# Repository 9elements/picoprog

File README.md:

# Picoprog

Picoprog is a firmware for the Raspberry Pi Pico and STM32 BluePill boards that provides a USB-to-serial and USB-to-SPI bridge. It allows you to communicate with UART and SPI peripherals via USB.

## Prerequisites

Before you can compile and use Picoprog, you need to install the following dependencies:

- Rust and Cargo: Follow the instructions on the [official Rust website](https://www.rust-lang.org/tools/install) to install Rust and Cargo.
- Install flip-link and elf2uf2

```sh
# Only Linux
sudo apt install build-essential libudev-dev pkg-config

# All systems
cargo install flip-link elf2uf2-rs
```

## Compiling the Firmware

To compile the firmware, follow these steps:

1. Clone the repository:

```sh
git clone https://github.com/9elements/picoprog.git
cd picoprog
```

2. Build the firmware for your target device:

For Raspberry Pi Pico:
```sh
cd picoprog
cargo run --release
```

For STM32 BluePill:
```sh
cd bluepill-prog
cargo run --release
```

3. The compiled binary will be located in:
   - Pico: `target/thumbv6m-none-eabi/release` directory
   - BluePill: `target/thumbv7m-none-eabi/release` directory

## Flashing the Firmware

### Raspberry Pi Pico

To flash the firmware onto the Raspberry Pi Pico, follow these steps:

1. Connect the Raspberry Pi Pico to your computer while holding the BOOTSEL button. This will put the Pico into USB mass storage mode.

2. Copy the UF2 file to the Pico:

```sh
# Linux
cp target/thumbv6m-none-eabi/release/picoprog.uf2 /media/$USER/RPI-RP2/

# macOS
cp target/thumbv6m-none-eabi/release/picoprog.uf2 /Volumes/RPI-RP2/
```

3. The Pico will automatically reboot and start running the new firmware.

### STM32 BluePill

To flash the firmware onto the STM32 BluePill, you'll need an ST-Link programmer or similar:

1. Connect the ST-Link to the BluePill's SWD pins (SWDIO, SWCLK, GND, 3.3V).

2. Have probe-rs installed

3. Use probe-rs with cargo
```sh
cd bluepill-prog
cargo run --release
```

## Usage

Once the firmware is running on the Raspberry Pi Pico, you can use any terminal program to communicate with the UART and SPI peripherals via USB. The device will appear as a USB CDC (Communications Device Class) device. Currently `/dev/ttyACM0` (macOS: `/dev/tty.usbmodemOSFC20241`) is a debug console that prints information about the picos current operation.

### UART Communication

To communicate with the UART peripheral, open the corresponding serial port (e.g., `/dev/ttyACM1` on Linux, `/dev/tty.usbmodemOSFC20243` on macOS) with your terminal program. For now the Baud is fixed at 115200 but can be changed in code. Dynamic reconfiguration is still planned.

### Using Flashrom or Flashprog

To interact with the Raspberry Pi Pico for reading and writing SPI flash chips, you can use tools like `flashrom` or `flashprog`. These tools support the `serprog` protocol, which allows communication over a serial interface.

1. Install `flashrom` or `flashprog` e.g.:

```sh
# Debian or Debian-based Linux distributions
sudo apt-get install flashrom

# macOS with Homebrew
brew install flashrom
```

2. Use the following command to read from the SPI flash chip:

```sh
flashrom -p serprog:dev=/dev/ttyACM2 -r backup.bin
```

This command reads the contents of the SPI flash chip and saves it to `backup.bin`.

3. Use the following command to write to the SPI flash chip:

```sh
flashrom -p serprog:dev=/dev/ttyACM2 -w firmware.bin
```

This command writes the contents of `firmware.bin` to the SPI flash chip.

Make sure to replace `/dev/ttyACM2` with the correct serial port if your device is connected to a different port or if you're on a different operating system (on macOS it will be `/dev/tty.usbmodemOSFC20245`).

## License

This project is licensed under the Apache 2.0 License. See the [LICENSE](LICENSE) file for details.

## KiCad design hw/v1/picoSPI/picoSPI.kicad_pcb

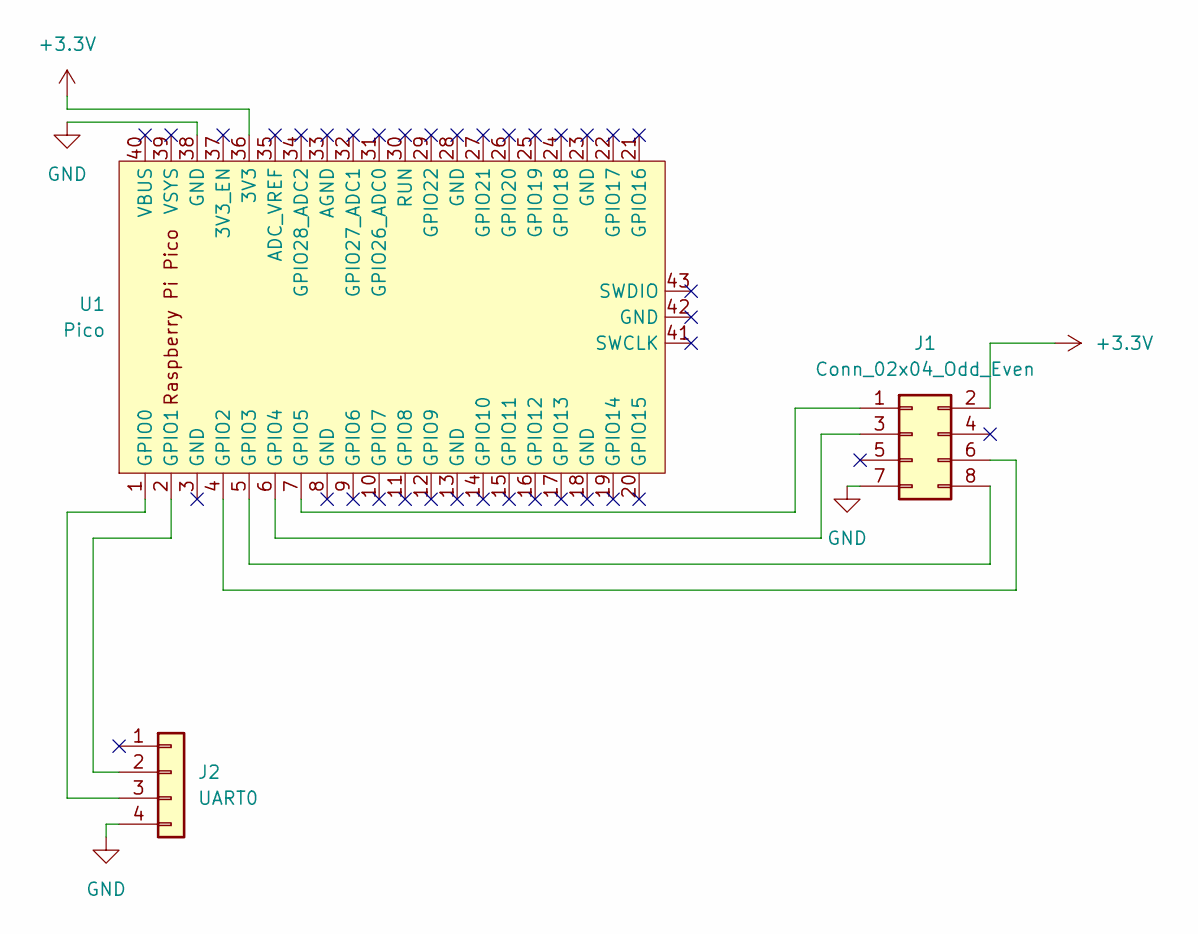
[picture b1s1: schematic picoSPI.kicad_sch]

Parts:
J1: Conn_02x04_Odd_Even; IDC-Header_2x04_P2.54mm_Vertical
J2: UART0; PinHeader_1x04_P2.54mm_Vertical
U1: Pico; RPi_Pico_SMD_TH

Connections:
+3.3V: J1.2, U1.36 (3V3)
GND: J1.7, J2.4, U1.38 (GND)
unnamed: J1.1, U1.7 (GPIO5)
unnamed: J1.3, U1.6 (GPIO4)
unnamed: J1.6, U1.4 (GPIO2)
unnamed: J1.8, U1.5 (GPIO3)
unnamed: J2.2, U1.2 (GPIO1)
unnamed: J2.3, U1.1 (GPIO0)

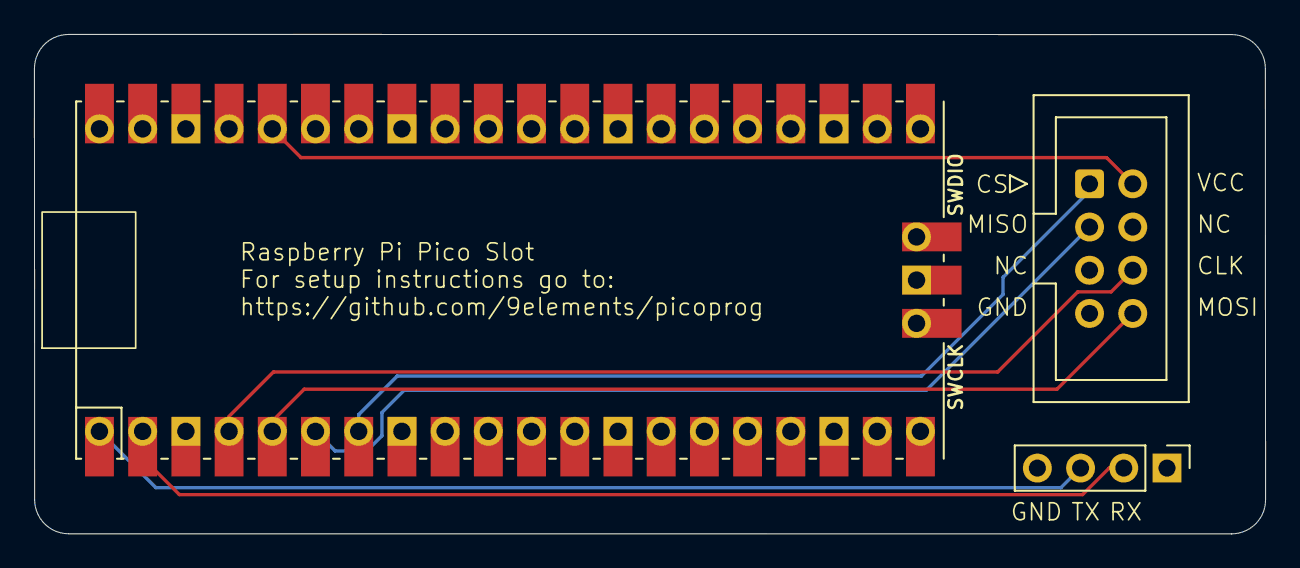
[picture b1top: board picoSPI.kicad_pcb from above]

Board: 2 copper layers, 72.4 x 29.4 mm, 4 parts (1 on the bottom side), 8 nets.

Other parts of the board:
9ESEC: LOGO; 9esec_8mm

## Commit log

2024-08-19 feat: initial code commit
2024-08-23 fix: add missing Cargo.toml flags and packages
2024-08-23 fix: fix UART task by using DMA
    The blocking UART messed too much with the task state so using
    the async DMA variant works a lot better, the only issue is
    the RX buffer size being extremely small.
2024-08-23 refactor: use log crate explicitly
2024-08-23 feat: change USB descriptor for OSFC
2024-08-23 feat: use async DMA SPI
    Same thing as with UART
2024-08-23 feat: toggle LED on serprog cmd
2024-08-23 fix: fix most serprog commands WIP
2024-08-26 Fix the array offset and endianness of SPI xfers
2024-08-26 chore: clean up debug logging
2024-08-29 fix: set correct QCmdMap resp buffer size
    This fixes the buffer size of QCmdMap and adds a flush
    call before the SPI transfer.
2024-08-29 fix: use spi write and read instead of transfer
2024-08-29 Remove wrong SPI CS command
    This command is about changing the SPI CS pin. We only support 1 pin.
2024-08-29 Set CS low and high for commands
2024-08-29 Implement QrdNMaxLen and QWrNMaxLen
    This makes sure flashrom does not send buffers that are too large.
2024-08-29 Fix setting SPI freq
    The command needs to return what frequency was actually set. Embassy has
    no API to return that so simply return the input.
2024-08-30 increase buffer size
    After some benchmarking it looks like reading speed flattens out at 2K.
    Benchmark results at 12M freq for a W25Q128:
    buffer size - read time in s
    256 43.85
    512 39.09
    1024 36.92
2024-08-30 Add probe-rs cargo-embed support
2024-08-30 chore: cleanup linter error
2024-08-30 feat: add CI workflows
2024-09-04 feat: add README
2024-09-04 feat(WIP): make array access a bit safer
2024-09-05 fix: attempt to fix uart glitches
    Makes it better but not perfect...
2024-09-05 docs: fix repo link from template
2024-09-06 docs: correct spelling of flashprog
2024-09-17 Add missing build dependencies
    The project README includes a list of commands for Ubuntu/Debian
    systems which are prequisites for building the Picoprog firmware.
    On a fresh install of Ubuntu, these are however not enough.
    This commit adds two more utilities required for a successful build.
2024-09-21 docs: Include some macOS-centric instructions
    Took me a little bit to figure out what to install and how to run
    things, figured I'd share it.
    I'm not actually sure the flashrom commands will actually succeed
    on macOS like this, as I don't have any memory chip available, but
    I can update the instructions when I do and there's something to fix.
2024-11-22 chore: uncomment import
2024-11-23 feat: add proper serial number programming
2025-02-06 fix: replace native UART with PIO
    This fixes the flakey UART by using the PIO peripheral
    with a UART implementation instead.
2025-02-06 fix: remove usage of unsafe to remove warning
2025-02-06 chore: bump all deps and toolchain
2025-02-10 style: Move uart code to a separate module
2025-02-10 style: Move the serprog logic into a separate file
2025-02-27 feat: Add zerocopy for some CMDs
2025-02-27 feat: Add other bits in CMD for reference
2025-02-27 style: Reduce boilerplate with num_enum
2025-02-27 feat: Use embedded hal traits in serprog.rs
    This makes it easy to reuse on a different project.
2025-02-27 feat: Implement setting SPISPEED via callback
2025-02-27 feat: Move seprog into a separate workspace
2025-02-27 refactor: Use top level workspace in sub-crates
2025-02-27 refactor: Move the top level loop into the serprog crate
2025-02-27 fix: Fix clippy issues
2025-02-27 style: Use more concise version of workspace deps
2025-02-27 feat: Add a transporter module in serprog
    This makes the module more reusable for high speed and other methods
    like serial and tcp.
2025-02-27 feat: Update embassy-rp
    The latest release should include that PR.
2025-02-27 chore: bump all deps
    This updates embassy and all the other crates with updates
    to their latest version
2025-02-27 feat: add pico carrier schematics
2025-02-28 Move .cargo/config.toml
2025-02-28 Add initial flashcrab fw
    This just builds. Nothing more, nothing less.
2025-02-28 chore: sort Cargo files
2025-03-04 feat: replace log crate with defmt
2025-03-12 fix: Move .cargo/config.toml
2025-03-12 fix: Move Embed.toml
    This is picoprog specific.
2025-03-12 feat: Add bluepill-prog (stm32f103)
    Not tested on flash chip yet but does not fail miserably.
    The API to use the CDC ACM seems to differ slightly from RP where
    waiting for connection needs to happen first.
2025-03-12 feat: Add spiconfig to bluepill
2025-03-12 docs: Add stm32 bluepill to README.md
2025-03-13 feat: Update CI files for both pico and bluepill
2025-05-07 fix: Use transfer instead of read + write
    One some hardware like stm32 it's not guaranteed to be one transaction.
2025-05-08 fix: move the error handling up the loop
    This returns early on problems too which is desirable.
2025-05-23 picoprog: use rtt and defmt for debug output
2025-05-23 fix: CI test
    Output dir is not relative with workspaces
2025-05-23 feat: do USB and SPI async
2025-05-23 fix: block on SPI + USB during SPI transaction
    This ensures the SPI keeps running.
2025-05-23 feat: Add probe-rs command for picoprog
    This is convenient.
2025-05-23 Move the SPI operation into a callback
    This makes it easier to provide non embedded_hal compliant peripherals
    like ospi or qspi implementations.
2025-05-23 Move a usb2 feature for larger packet size
2025-05-23 Move the spi op callback into an option
    Progress towards a new MultiIOSpi CMD.
2025-05-23 Prepare multi IO commands
2025-06-09 ci: Add tombi ci form toml file
    https://tombi-toml.github.io/tombi seems like a great tool.
2025-06-12 WIP Add flashcrab
2025-06-20 feat(serprog): Refactor USB communication using channels
    - Replace direct USB transport with channel-based communication
    - Add new USB task for handling USB I/O operations
    - Implement channel-based command and response handling
    - Simplify SPI operation handling with direct USB communication
    - Remove old transport module and add new usb_task module
    Using sync datastructures makes it simpler to implement variations than
2025-06-20 feat(spi): Add trait for changing SPI frequency dynamically
    This commit introduces the `ChangeSpiFreq` trait to allow dynamic
    modification of SPI frequencies. Implementations for `StmSpi` and
    `RpSpi` are added, and the `Serprog` struct is updated to use this trait
    instead of a callback. This simplifies the code and ensures consistent
    handling of frequency changes across different SPI implementations.
2025-06-20 refactor(serprog): Make SPI optional and add NoSpi implementation
    This commit modifies the `Serprog` struct to make the SPI field
    optional, allowing the program to run without SPI functionality. A new
    `NoSpi` module is added to provide a no-op SPI implementation for cases
    where SPI is not available. The `OSpiOp` and `SSpiFreq` commands now
    check for SPI availability and return appropriate responses if SPI is
    not present.
2025-06-20 feat(spi): Add support for Multi-IO SPI modes and operations
    This commit introduces new enums, structs, and bitfields to support
    Multi-IO SPI modes and operations. It includes the `MultiIOMode` enum,
    `MultiIOSpiHeader` and `QMultiIOSpiModesResponse` structs, and extends
    the `SerprogCommand` enum with `QMultiIOSpiModes` and `MultiIOSpiOp`
    commands. Additionally, it adds the `IOModeAndDirection` bitfield to
    handle IO mode and direction flags.
2025-06-20 feat(flashcrab): Add Flashcrab project with OSPI and USB support
    This commit introduces a new project called Flashcrab, which includes
    support for OSPI (OctoSPI) flash memory operations and USB
    communication. The project also includes integration tests for various
    hardware functionalities such as DAC, hardware hashing, and LED sequence
    control. The build system is configured with Flip Link for the Thumbv8m
    target, and the project is set up for embedded testing.
2025-06-20 feat(ospi): Add OspiWrapper and integrate with serprog
    This commit introduces the `OspiWrapper` struct to work around orphan
    rules and implements the `MultiIOSpi` trait for it. The struct provides
    methods to build transfer configurations and handle reset, read, and
    write operations for OSPI (Octo-SPI) transactions.
    The `serprog` integration is updated to use `OspiWrapper` instead of a
    dummy SPI implementation. Additionally, the `vbus_detection`
2025-06-20 feat(serprog): Add Multi-IO SPI support
    This commit introduces Multi-IO SPI functionality to the serprog module,
    enabling support for advanced SPI modes like Dual I/O, Quad I/O, and
    QPI. It includes a new `multi_io_spi` module, updates to the `Serprog`
    struct to handle Multi-IO SPI transactions, and new
    commands (`QMultiIOSpiModes`, `MultiIOSpiOp`) for protocol interaction.
    The changes also ensure compatibility with existing SPI operations while
2025-06-20 Make things asyn
2025-06-20 feat(cs_control): Add CS control trait and implementation
    - Introduces new CsControl trait for chip select management
    - Provides NoCs implementation for no-op CS control
    = Implements CsControl for OutputPin with single CS support
    - Updates Serprog struct to use CsControl trait
    - Adds SSpiCs command handling for CS selection
2025-09-14 Fix build instructions for Raspberry Pi Pico
    Added instructions to enter the `picoprog` directory when building for Raspberry Pi Pico
2025-09-20 core: Update crates
    Update the crates to their latest version
2025-10-17 Add ch32v307 based programmer
    Setting the USB buffer sizes to 512 works, however using anything that
    is not 64 bytes inside the serprog lib fails weirdly. It just hangs at
    some point...
2025-10-21 Add method for IDLE SPI and CS
2025-12-17 feat: Use heapless Vec + zerocopy for the first 64 bytes
2025-12-17 feat: Move SPI and USB tasks into async functions
    This increases readability as indentation is reduced.
2025-12-17 feat: Move transfer size to generics
2025-12-17 refactor: Lazily acquire SPI device to avoid interfering with target board
    Replace the static `Serprog` struct with a trait-based approach where
    SPI pins are only configured as outputs during actual SPI operations:
    - Add `SpiDeviceProvider` trait for on-demand SPI device creation
    - Add `SpiCsGuard` trait for guards that provide SPI+CS access
    - Add `LedProvider` trait with blanket impl for any `OutputPin`
    - Replace `Serprog::run_loop()` with free function `run_loop()`
2025-12-17 Add timeouts to USB operations
    If the host decides to halt an operation previously we needed to reset
    the device. Now we have a reasonable timeout upon which the device goes
    back to a state in which it can accept further commands.
2025-12-22 fix: Address Copilot code review feedback
    - Fix channel protocol by calling send().await before send_done()
    - Handle resize() errors explicitly instead of ignoring with .ok()
    - Fix incorrect error message 'SBustype ACK' -> 'OSpiOp ACK'
    - Replace try_into().unwrap() with direct 'as u16' cast for USB buffer size
